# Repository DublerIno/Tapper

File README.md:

# Tapper
Simple BPM counter and metronome on custom board, replacing apps filled with Ads. 
STM32G030F6P6 TSSOP20 as a brain. MX Cherry switch for satisfying click. OLED for visuals. 

## GOAL
This simple project may seem like reinventing the wheel, but my main goal is to learn:
- STM32 Programming pipeline
- Custom PCB design for embedded systems
- Microsoldering 

### STM32G030F6P6 Dev Board
Currently, I am working on my custom development board to test the following features:
- STlink connection
- USBC connection with CH340E for UART
- Battery charging circuit for LiPo with MCP73831
- OLED test circuit
- STM32 pinouts

### Current status
- PCB done
- Soldering done
- Circuit testing successful
- Now programming..

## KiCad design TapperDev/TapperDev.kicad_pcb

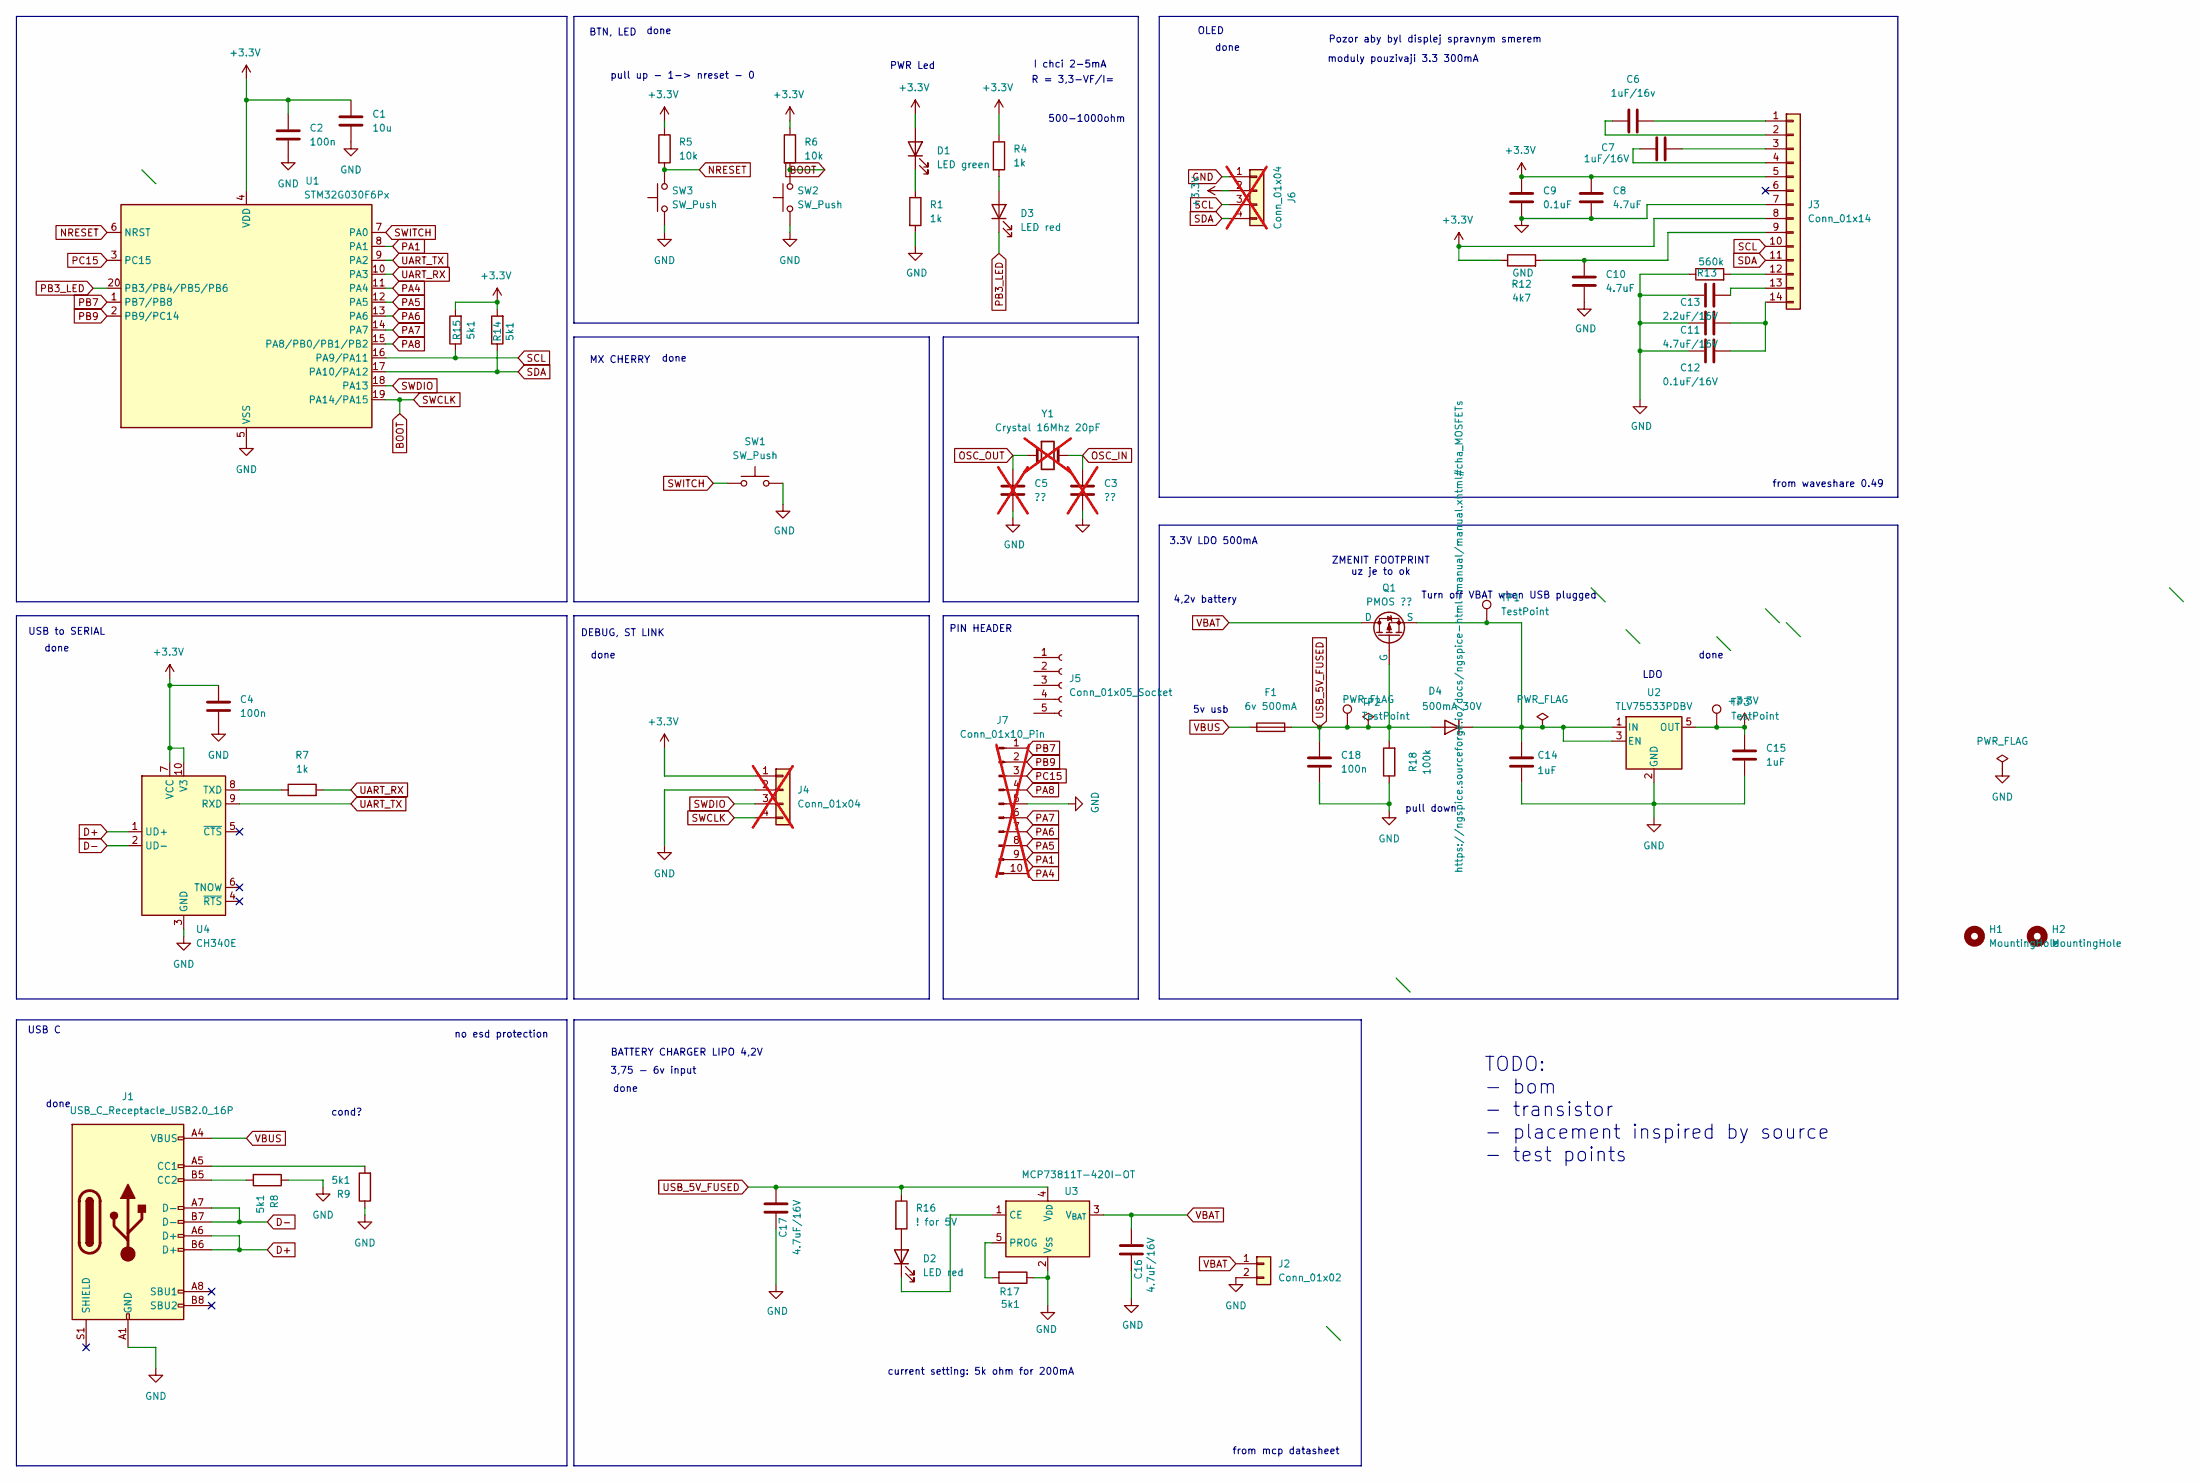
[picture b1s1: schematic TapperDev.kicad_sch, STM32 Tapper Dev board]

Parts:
C1: 10u; C_0603_1608Metric_Pad1.08x0.95mm_HandSolder
C2, C4, C18: 100n; C_0603_1608Metric_Pad1.08x0.95mm_HandSolder
C3, C5: ??; C_0603_1608Metric_Pad1.08x0.95mm_HandSolder; not fitted
C6: 1uF/16v; C_0603_1608Metric_Pad1.08x0.95mm_HandSolder
C7: 1uF/16V; C_0603_1608Metric_Pad1.08x0.95mm_HandSolder
C8, C10: 4.7uF; C_0603_1608Metric_Pad1.08x0.95mm_HandSolder
C9: 0.1uF; C_0603_1608Metric_Pad1.08x0.95mm_HandSolder
C11, C16, C17: 4.7uF/16V; C_0603_1608Metric_Pad1.08x0.95mm_HandSolder
C12: 0.1uF/16V; C_0603_1608Metric_Pad1.08x0.95mm_HandSolder
C13: 2.2uF/16V; C_0603_1608Metric_Pad1.08x0.95mm_HandSolder
C14, C15: 1uF; C_0603_1608Metric_Pad1.08x0.95mm_HandSolder
D1: LED green; D_0603_1608Metric_Pad1.05x0.95mm_HandSolder
D2, D3: LED red; D_0603_1608Metric_Pad1.05x0.95mm_HandSolder
D4: 500mA 30V; Nexperia_CFP3_SOD-123W
F1: 6v 500mA; Fuse_0603_1608Metric
H1, H2: MountingHole; MountingHole_2.2mm_M2
J1: USB_C_Receptacle_USB2.0_16P; USB_C_Receptacle_XKB_U262-16XN-4BVC11
J2: Conn_01x02; PinSocket_1x02_P2.54mm_Vertical
J3: Conn_01x14; TE_1-84952-4_1x14-1MP_P1.0mm_Horizontal
J4: Conn_01x04; PinSocket_1x04_P2.54mm_Vertical; not fitted
J5: Conn_01x05_Socket
J6: Conn_01x04; PinSocket_1x04_P1.27mm_Vertical; not fitted
J7: Conn_01x10_Pin; PinSocket_1x10_P1.27mm_Vertical; not fitted
Q1: PMOS ??; SOT-23
R1, R4, R7: 1k; R_0603_1608Metric_Pad0.98x0.95mm_HandSolder
R5, R6: 10k; R_0603_1608Metric_Pad0.98x0.95mm_HandSolder
R8, R9, R14, R15, R17: 5k1; R_0603_1608Metric_Pad0.98x0.95mm_HandSolder
R12: 4k7; R_0603_1608Metric_Pad0.98x0.95mm_HandSolder
R13: 560k; R_0603_1608Metric_Pad0.98x0.95mm_HandSolder
R16: ! for 5V; R_0603_1608Metric_Pad0.98x0.95mm_HandSolder
R18: 100k; R_0603_1608Metric_Pad0.98x0.95mm_HandSolder
SW1: SW_Push; SW_Cherry_MX_PCB
SW2, SW3: SW_Push; SW_Tactile_SPST_NO_Straight_CK_PTS636Sx25SMTRLFS
TP1, TP2, TP3: TestPoint; TestPoint_Pad_1.5x1.5mm
U1: STM32G030F6Px; TSSOP-20_4.4x6.5mm_P0.65mm
U2: TLV75533PDBV; SOT-23-5
U3: MCP73811T-420I-OT; SOT-23-5
U4: CH340E; MSOP-10_3x3mm_P0.5mm
Y1: Crystal 16Mhz 20pF; Crystal_HC49-U_Vertical; not fitted

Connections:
+3.3V: C1.1, C2.1, C4.1, C8.1, C9.1, C15.1, D1.2 (A), J3.5, J3.8, J4.1, J6.2, R4.1, R5.1, R6.1, R12.1, R14.2, R15.2, TP3.1, U1.4 (VDD), U2.5 (OUT), U4.7 (VCC), U4.10 (V3)
BOOT: J4.4, R6.2, SW2.2, U1.19 (PA14/PA15)
D+: J1.A6 (D+), J1.B6 (D+), U4.1 (UD+)
D-: J1.A7 (D-), J1.B7 (D-), U4.2 (UD-)
GND: C1.2, C2.2, C3.2, C4.2, C5.2, C8.2, C9.2, C10.2, C11.2, C12.1, C13.2, C14.2, C15.2, C16.2, C17.2, C18.2, J1.A1 (GND), J1.A12 (GND), J1.B1 (GND), J1.B12 (GND), J2.2, J3.7, J4.2, J6.1, J7.5, R1.2, R8.1, R9.1, R13.1, R17.1, R18.1, SW1.2, SW2.1, SW3.1, U1.5 (VSS), U2.2 (GND), U3.2 (V_{SS}), U4.3 (GND)
NRESET: R5.2, SW3.2, U1.6 (NRST)
unnamed: C3.1, Y1.2
unnamed: C5.1, Y1.1
unnamed: D1.1 (K), R1.1
unnamed: D2.2 (A), R16.2
unnamed: D2.1 (K), U3.1 (CE)
unnamed: D3.2 (A), R4.2
unnamed: C14.1, D4.1 (K), Q1.2 (S), TP1.1, U2.1 (IN), U2.3 (EN)
unnamed: J1.A5 (CC1), R9.2
unnamed: J1.B5 (CC2), R8.2
unnamed: C6.2, J3.1
unnamed: C6.1, J3.2
unnamed: C7.2, J3.3
unnamed: C7.1, J3.4
unnamed: C10.1, J3.9, R12.2
unnamed: J3.12, R13.2
unnamed: C13.1, J3.13
unnamed: C11.1, C12.2, J3.14
unnamed: R17.2, U3.5 (PROG)
unnamed: R7.1, U4.8 (TXD)
PA1: J7.9, U1.8 (PA1)
PA4: J7.10, U1.11 (PA4)
PA5: J7.8, U1.12 (PA5)
PA6: J7.7, U1.13 (PA6)
PA7: J7.6, U1.14 (PA7)
PA8: J7.4, U1.15 (PA8/PB0/PB1/PB2)
PB3_LED: D3.1 (K), U1.20 (PB3/PB4/PB5/PB6)
PB7: J7.1, U1.1 (PB7/PB8)
PB9: J7.2, U1.2 (PB9/PC14)
PC15: J7.3, U1.3 (PC15)
SCL: J3.10, J6.3, R15.1, U1.16 (PA9/PA11)
SDA: J3.11, J6.4, R14.1, U1.17 (PA10/PA12)
SWDIO: J4.3, U1.18 (PA13)
SWITCH: SW1.1, U1.7 (PA0)
UART_RX: R7.2, U1.10 (PA3)
UART_TX: U1.9 (PA2), U4.9 (RXD)
USB_5V_FUSED: C17.1, C18.1, D4.2 (A), F1.2, Q1.1 (G), R16.1, R18.2, TP2.1, U3.4 (V_{DD})
VBAT: C16.1, J2.1, Q1.3 (D), U3.3 (V_{BAT})
VBUS: F1.1, J1.A4 (VBUS), J1.A9 (VBUS), J1.B4 (VBUS), J1.B9 (VBUS)

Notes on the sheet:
ZMENIT FOOTPRINT uz je to ok
from waveshare 0.49
done
4,2v battery
500-1000ohm
no esd protection
from mcp datasheet
USB to SERIAL
PIN HEADER
USB C
MX CHERRY
I chci 2-5mA
BTN, LED
PWR Led
pull down
DEBUG, ST LINK
5v usb
cond?
OLED
3,75 - 6v input
current setting: 5k ohm for 200mA
BATTERY CHARGER LIPO 4,2V
Pozor aby byl displej spravnym smerem
LDO
TODO: - bom - transistor - placement inspired by source - test points
R = 3,3-VF/I=
pull up - 1-> nreset - 0
Turn off VBAT when USB plugged
3.3V LDO 500mA
moduly pouzivaji 3.3 300mA

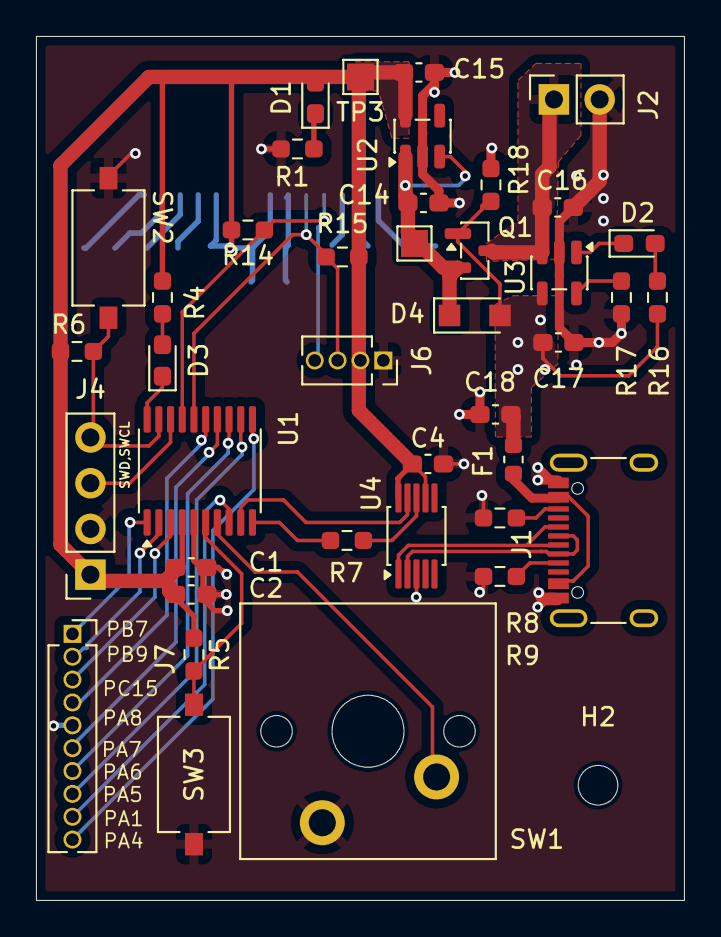
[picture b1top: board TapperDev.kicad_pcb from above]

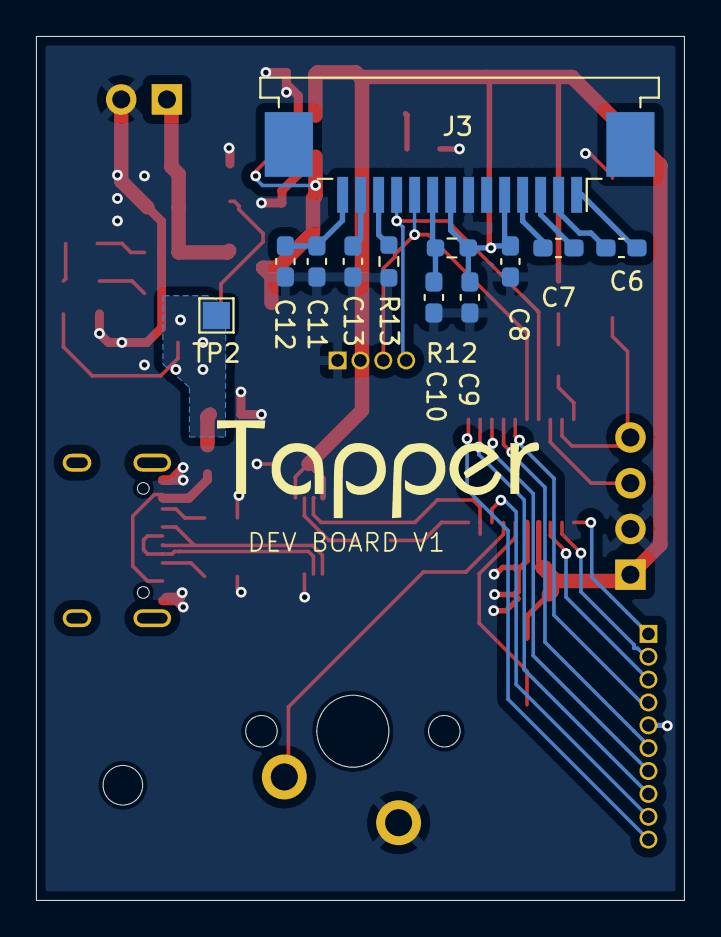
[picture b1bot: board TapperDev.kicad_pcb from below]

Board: 2 copper layers, 36.0 x 48.0 mm, 53 parts (12 on the bottom side), 42 nets.

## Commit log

2026-01-18 Correct image link in README.md
    Fixed image link formatting in README.
2026-01-18 Fix image link in README.md
    Updated image link in README for the first dev board.
2026-01-18 Fix image markdown syntax in README.md
2026-02-08 Revise README with project goals and details
    Updated project description and goals in README.
2026-02-08 Revise STM32G030F6P6 Dev Board features and image
    Updated the features list for the STM32G030F6P6 Dev Board and improved the image caption.
2026-02-08 added kicad project files
2026-02-08 Update README with current project status
    Added current status of the development board project.
